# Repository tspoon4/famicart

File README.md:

# Overview
A while ago, I bought a Famicom in Japan with a bunch of game carts (including Super Mario Bros. 3 and The Legend of Zelda 1!).

As a programmer, I always had in mind to run my own program on it and play with this amazing hardware.
As a beginner in electronics, designing a development cartridge would be an great opportunity to learn.

After a bit of googling, I found the Nesdev community and their extensive [knowledge base](http://wiki.nesdev.com/w/index.php/Nesdev_Wiki). For this learning project, I wanted to design the board from scratch by choosing myself the components and discovering the boolean logic to connect them.

I enjoyed studying the various IC datasheets and playing with the Arduino to prototype the PRG-ROM Flasher.
Please note that this project is not optimized for cost and is not a professional development platform.

# Features
* 512KiB PRG-ROM (Flash) split in 16x32KiB banks
* 64KiB PRG-RAM (SRAM) split in 8x8KiB banks, battery backed work RAM
* 16KiB CHR-RAM (SRAM) with 2-4 nametable support
* Simple discrete logic mapper using an 8bit write-only register at address $8000
	* Bit 0-3: PRG-ROM 32KiB bank selection (2^4 = 16)
	* Bit 4-6: PRG-RAM 8KiB bank selection (2^3 = 8)
	* Bit 7: Software mirroring control (horizontal, vertical)
* CHR-RAM memory mapping customization with 2 jumpers
	* Jumper J2: CIRAM enable/disable
	* Jumper J3: Software controlled mirroring/single-screen
* Arduino Uno/Nano PRG-ROM programmer is available at this [location](flash/)
* KiCad source files for modification are available at this [location](kicad/)
* PDF exports for quick review are available at this [location](pdf/)

# Pictures
Images | Images
------ | ------
 | 
 | 

# Production
To produce the PCB that will fit in the Famicom cartridge slot, you will have to provide to the manufacturer the 2 following items:
* Information that the PCB thickness should be **1.2mm**
* The Gerber files for the different PCB layers from this [location](gerber/)

# Components
Reference | Quantity | Purpose
--------- | -------- | -------
Resistor 1k | 1 | Battery charge protection
Resistor 10k | 1 | Pull down for PRG-RAM
Diode 1N4148 | 2 | Or PRG-RAM power supply
Capacitor 100nF | 7 | Decoupling
Nand 74HC00 | 2 | Decoding PRG R/W signals and misc logic
Nor 74HC02 | 1 | Software controlled mirroring logic
Latch 74HC573 | 1 | Mapper register
Flash SST39SF040 | 1 | PRG-ROM chip
SRAM uPD431000A-70LL | 2 | PRG-RAM and CHR-RAM chip
Conn 3pins | 2 | CHR-RAM jumpers
CR2032 Holder | 1 | 3V battery case

# Potential improvements
### Palette RAM bus conflict when disabling CIRAM
When disabling CIRAM the CHR-RAM is always enabled because:
* CHR-RAM /CE1 is connected to GND
* CHR-RAM CE2 is connected to VCC

CHR-RAM read/write technically mirrors Palette RAM indices but this has not been extensively tested.
### Component packing
Packing is loose and PCB surface use can be improved to reduce costs and fit in a cartridge case.
Vias close to the cartridge connectors might be saved by leveraging memory chip pads.
### CHR-RAM banks instead of PRG-RAM
I've made the choice to implement banking on PRG-RAM instead of CHR-RAM.
It is possible to modify the KiCad source files to use Bit 4-6 of the mapper register to implement banking on CHR-RAM the same way as PRG-RAM.

# References
* [Nesdev wiki](https://wiki.nesdev.com/w/index.php/Cartridge_connector) for the cartridge connector pinout
* [Nesdev forums](https://forums.nesdev.com/viewtopic.php?f=9&t=2162) for the PCB specs and various information
* [KiCad EDA](https://kicad.org/) to edit the PCB source files
* [Arduino Nano](https://store.arduino.cc/usa/arduino-nano) for the links on datasheets
* [NES ca65 example](https://github.com/bbbradsmith/NES-ca65-example) to validate the cartridge features 
* IC Datasheets (TI, SST, NEC)

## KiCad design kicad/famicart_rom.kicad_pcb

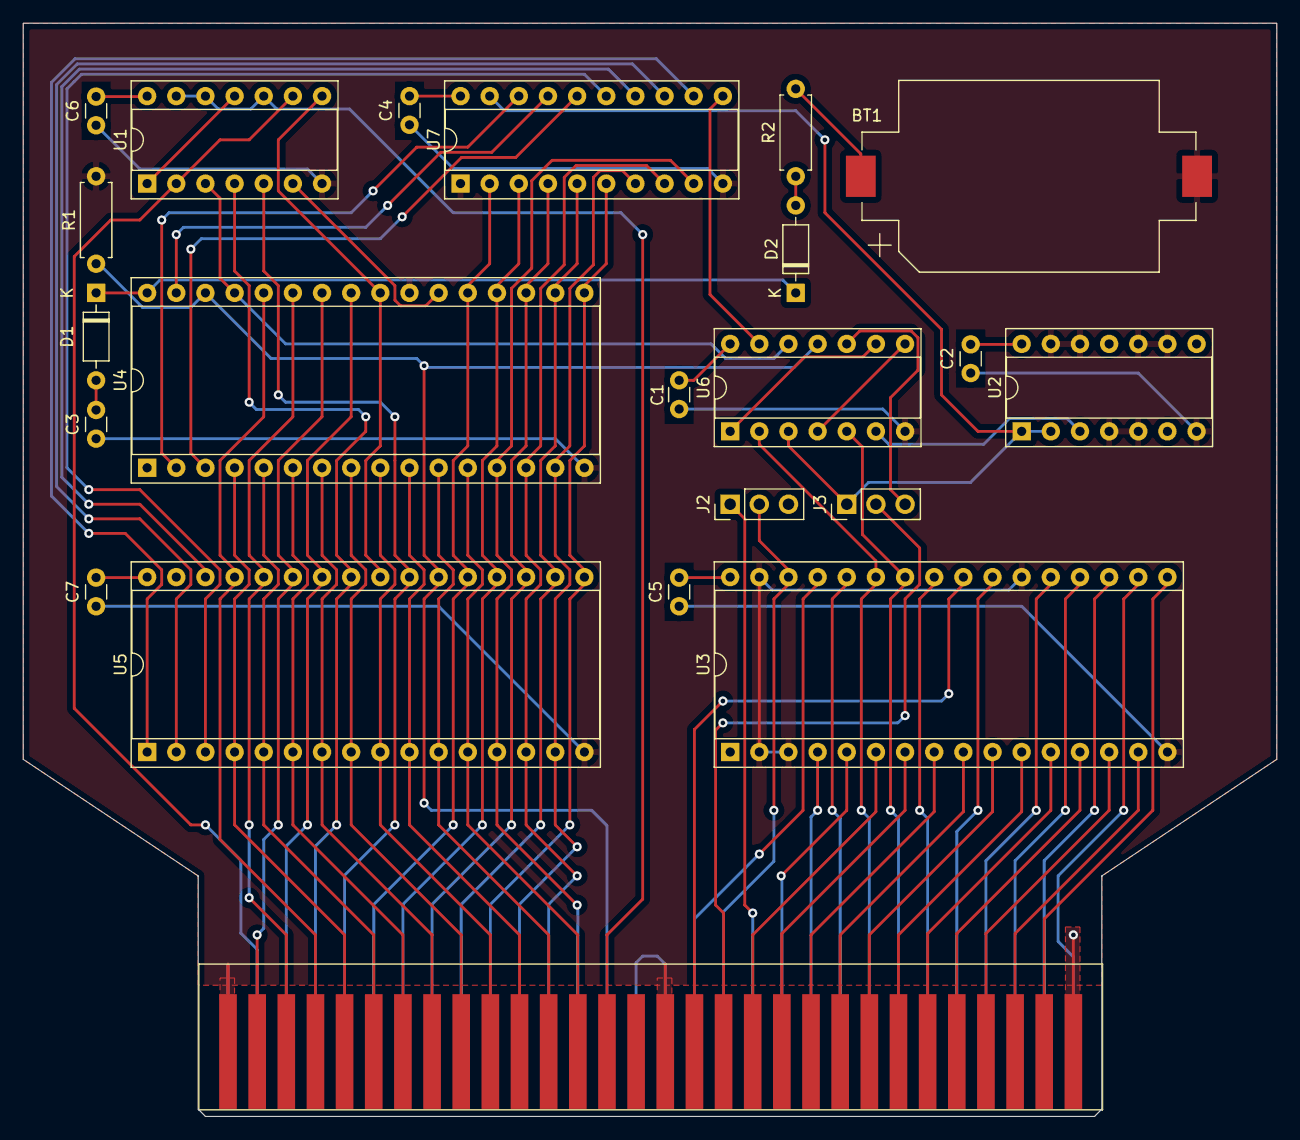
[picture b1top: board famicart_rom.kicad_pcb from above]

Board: 2 copper layers, 109.2 x 95.2 mm, 22 parts (0 on the bottom side), 76 nets.

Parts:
BT1: Battery_Cell; BatteryHolder_Keystone_1060_1x2032
C1, C2, C3, C4, C5, C6, C7: 100nF; C_Disc_D3.0mm_W1.6mm_P2.50mm
D1, D2: 1N4148; D_DO-35_SOD27_P7.62mm_Horizontal
J1: Conn_Famicom_Cart; famicom_cart
J2, J3: Conn_01x03; PinHeader_1x03_P2.54mm_Vertical
R1: R10k; R_Axial_DIN0207_L6.3mm_D2.5mm_P7.62mm_Horizontal
R2: R1k; R_Axial_DIN0207_L6.3mm_D2.5mm_P7.62mm_Horizontal
U1, U2: 74HC00; DIP-14_W7.62mm_Socket
U3, U4: uPD431000A; DIP-32_W15.24mm_Socket
U5: SST39SF040; DIP-32_W15.24mm_Socket
U6: 74HC02; DIP-14_W7.62mm_Socket
U7: 74HC573; DIP-20_W7.62mm_Socket

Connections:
/A10_SEL: U6.1, U6.9
/A11_SEL: U6.4, U6.8
/AUDIO_IN: J1.45, J1.46
/CIRAM_A10: J1.18, J3.2
/CIRAM_nCE: J1.48, J2.2, U3.30
/CPU_A0: J1.13, U4.12, U5.12
/CPU_A1: J1.12, U4.11, U5.11
/CPU_A2: J1.11, U4.10, U5.10
/CPU_A3: J1.10, U4.9, U5.9
/CPU_A4: J1.9, U4.8, U5.8
/CPU_A5: J1.8, U4.7, U5.7
/CPU_A6: J1.7, U4.6, U5.6
/CPU_A7: J1.6, U4.5, U5.5
/CPU_A8: J1.5, U4.4, U5.4
/CPU_A9: J1.4, U4.28, U5.29
/CPU_A10: J1.3, U4.27, U5.28
/CPU_A11: J1.2, U4.26, U5.27
/CPU_A12: J1.33, U4.25, U5.26
/CPU_A13: J1.34, U1.4, U5.25
/CPU_A14: J1.35, U1.5, U5.23
/CPU_D0: J1.43, U4.13, U5.13, U7.9
/CPU_D1: J1.42, U4.14, U5.14, U7.8
/CPU_D2: J1.41, U4.15, U5.15, U7.7
/CPU_D3: J1.40, U4.17, U5.17, U7.6
/CPU_D4: J1.39, U4.18, U5.18, U7.5
/CPU_D5: J1.38, U4.19, U5.19, U7.4
/CPU_D6: J1.37, U4.20, U5.20, U7.3
/CPU_D7: J1.36, U4.21, U5.21, U7.2
/CPU_RnW: J1.14, U1.10, U1.12, U1.13
/M2: J1.32, U1.2, U1.9
/MAP_D0: U5.1, U7.12
/MAP_D1: U5.2, U7.13
/MAP_D2: U5.30, U7.14
/MAP_D3: U5.3, U7.15
/MAP_D4: U4.3, U7.16
/MAP_D5: U4.31, U7.17
/MAP_D6: U4.2, U7.18
/MAP_D7: J3.1, U2.1, U2.2, U6.3, U7.19
/MAP_LE: U6.13, U7.11
/MAP_MIR: J3.3, U6.10
/MAP_nD7: U2.3, U6.6
/PPU_A0: J1.25, U3.12
/PPU_A1: J1.24, U3.11
/PPU_A2: J1.23, U3.10
/PPU_A3: J1.22, U3.9
/PPU_A4: J1.21, U3.8
/PPU_A5: J1.20, U3.7
/PPU_A6: J1.19, U3.6
/PPU_A7: J1.50, U3.5
/PPU_A8: J1.51, U3.4
/PPU_A9: J1.52, U3.28
/PPU_A10: J1.53, U3.27, U6.2
/PPU_A11: J1.54, U3.26, U6.5
/PPU_A12: J1.55, U3.25
/PPU_A13: J1.56, U3.23
/PPU_D0: J1.26, U3.13
/PPU_D1: J1.27, U3.14
/PPU_D2: J1.28, U3.15
/PPU_D3: J1.29, U3.17
/PPU_D4: J1.60, U3.18
/PPU_D5: J1.59, U3.19
/PPU_D6: J1.58, U3.20
/PPU_D7: J1.57, U3.21
/PPU_nA13: J1.49, J2.1
/PPU_nRD: J1.17, U3.24
/PPU_nWR: J1.47, U3.29
/PRG_nOE: U1.8, U4.24, U5.24
/PRG_nWE: U1.3, U4.29, U6.12
/VBAT: D1.1, D2.1, U4.32
/WRK_nCE: U1.6, U4.22
/nROMSEL: J1.44, R1.1, U4.30, U5.22, U6.11
GND: BT1.2, C1.2, C2.1, C3.1, C4.1, C5.1, C6.1, C7.1, J1.1, J1.16, R1.2, U1.7, U2.4, U2.5, U2.7, U2.9, U2.10, U2.12, U2.13, U3.2, U3.3, U3.16, U3.22, U3.31, U4.16, U4.23, U5.16, U6.7, U7.1, U7.10
unnamed: BT1.1, R2.2
unnamed: D2.2, R2.1
unnamed: U1.1, U1.11
VCC: C1.1, C2.2, C3.2, C4.2, C5.2, C6.2, C7.2, D1.2, J1.30, J1.31, J2.3, U1.14, U2.14, U3.32, U5.31, U5.32, U6.14, U7.20

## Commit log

2021-01-18 Test first commit
2021-03-22 Add most of the content, still have to complete *.md files
2021-03-22 Attempt to show images directly
2021-03-22 Attempt to show images directly(2)
2021-04-04 Additions to README.md
2021-04-04 Fix issues in README.md
2021-04-05 Added flash program README.md
2021-04-05 Attempt to fix flash README
2021-04-05 Attempt 2 to fix flash README
2021-04-05 Add more details to flash README
2021-04-05 Integrated jero32 feedback: pdf export and connector mask update
2021-04-05 Fixed image path in flash README
